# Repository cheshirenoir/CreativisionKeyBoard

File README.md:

# CreativisionKeyBoard
Replacement Moving Key Keyboard for the VTech Creativision, AKA the Dick Smith Wizzard

An attempt to map the Moving Key Keyboard then convert it into a functional PCB 

This design is released under a CC-BY-SA license. Remix, but always share!

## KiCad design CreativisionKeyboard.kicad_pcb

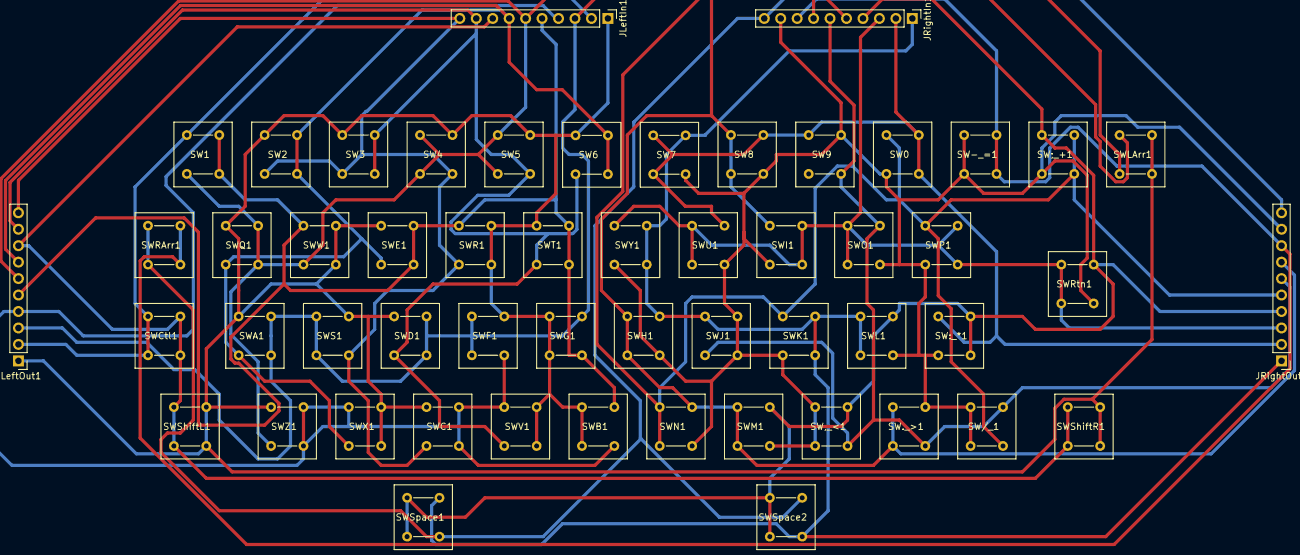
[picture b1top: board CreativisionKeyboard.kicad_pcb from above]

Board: 2 copper layers, 54 parts (0 on the bottom side), 20 nets.

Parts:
JLeftIn1: Conn_01x10_Female; PinHeader_1x10_P2.54mm_Vertical
JLeftOut1: Conn_01x10_Female; PinHeader_1x10_P2.54mm_Vertical
JRightIn1: Conn_01x10_Female; PinHeader_1x10_P2.54mm_Vertical
JRightOut1: Conn_01x10_Female; PinHeader_1x10_P2.54mm_Vertical
SW0: 0; pva1oah31.2nv2
SW1: 1; pva1oah31.2nv2
SW2: 2; pva1oah31.2nv2
SW3: 3; pva1oah31.2nv2
SW4: 4; pva1oah31.2nv2
SW5: 5; pva1oah31.2nv2
SW6: 6; pva1oah31.2nv2
SW7: 7; pva1oah31.2nv2
SW8: 8; pva1oah31.2nv2
SW9: 9; pva1oah31.2nv2
SW,_<1: Comma LT; pva1oah31.2nv2
SW-_=1: Minus Equals; pva1oah31.2nv2
SW._>1: Period GT; pva1oah31.2nv2
SW/_1: Slash QMark; pva1oah31.2nv2
SW:_*1: Colon Star; pva1oah31.2nv2
SW;_+1: SemiColon Plus; pva1oah31.2nv2
SWA1: A; pva1oah31.2nv2
SWB1: B; pva1oah31.2nv2
SWC1: C; pva1oah31.2nv2
SWCtl1: Ctrl; pva1oah31.2nv2
SWD1: D; pva1oah31.2nv2
SWE1: E; pva1oah31.2nv2
SWF1: F; pva1oah31.2nv2
SWG1: G; pva1oah31.2nv2
SWH1: H; pva1oah31.2nv2
SWI1: I; pva1oah31.2nv2
SWJ1: J; pva1oah31.2nv2
SWK1: K; pva1oah31.2nv2
SWL1: L; pva1oah31.2nv2
SWLArr1: <-; pva1oah31.2nv2
SWM1: M; pva1oah31.2nv2
SWN1: N; pva1oah31.2nv2
SWO1: O; pva1oah31.2nv2
SWP1: P; pva1oah31.2nv2
SWQ1: Q; pva1oah31.2nv2
SWR1: R; pva1oah31.2nv2
SWRArr1: ->; pva1oah31.2nv2
SWRtn1: Return; pva1oah31.2nv2
SWS1: S; pva1oah31.2nv2
SWShiftL1: Shift Left; pva1oah31.2nv2
SWShiftR1: Shift Righ; pva1oah31.2nv2
SWSpace1, SWSpace2: Space; pva1oah31.2nv2
SWT1: T; pva1oah31.2nv2
SWU1: U; pva1oah31.2nv2
SWV1: V; pva1oah31.2nv2
SWW1: W; pva1oah31.2nv2
SWX1: X; pva1oah31.2nv2
SWY1: Y; pva1oah31.2nv2
SWZ1: Z; pva1oah31.2nv2

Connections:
unnamed: JLeftIn1.1, JLeftOut1.1, SW2.1, SW3.1, SW4.2, SW5.2, SW6.1, SWA1.1, SWB1.1, SWB1.3, SWC1.1, SWD1.1, SWE1.1, SWF1.2, SWG1.1, SWG1.3, SWLArr1.2, SWLArr1.4, SWQ1.1, SWR1.2, SWR1.4, SWS1.2, SWShiftL1.2, SWShiftL1.4, SWShiftR1.2, SWShiftR1.4, SWT1.1, SWV1.2, SWV1.4, SWW1.2, SWW1.4, SWX1.2, SWX1.4, SWZ1.1
unnamed: JLeftIn1.2, JLeftOut1.2, SW1.1, SWCtl1.1, SWCtl1.3
unnamed: JLeftIn1.3, JLeftOut1.3, SWA1.2, SWA1.4, SWD1.2, SWD1.4, SWF1.1, SWF1.3, SWG1.2, SWLArr1.1, SWS1.1, SWS1.3
unnamed: JLeftIn1.4, JLeftOut1.4, SWB1.4, SWC1.2, SWC1.4, SWF1.4, SWV1.1, SWX1.1, SWZ1.2, SWZ1.4
unnamed: JLeftIn1.5, JLeftOut1.5, SW1.2, SW1.4, SWB1.2, SWE1.2, SWE1.4, SWG1.4, SWR1.1, SWT1.2, SWT1.4, SWW1.1
unnamed: JLeftIn1.6, JLeftOut1.6, SW1.3, SW4.1, SW4.3, SW5.1, SW5.3, SWLArr1.3, SWQ1.2, SWQ1.4, SWW1.3, SWZ1.3
unnamed: JLeftIn1.7, JLeftOut1.7, SW2.2, SW2.4, SW6.2, SW6.4, SWA1.3, SWE1.3, SWQ1.3, SWX1.3
unnamed: JLeftIn1.8, JLeftOut1.8, SWCtl1.2, SWCtl1.4, SWShiftL1.1, SWShiftL1.3, SWShiftR1.1, SWShiftR1.3
unnamed: JLeftIn1.9, JLeftOut1.9, SW3.2, SW3.4, SW5.4, SW6.3, SWD1.3, SWT1.3, SWV1.3
unnamed: JLeftIn1.10, JLeftOut1.10, SW2.3, SW3.3, SW4.4, SWC1.3, SWR1.3, SWS1.4
unnamed: JRightIn1.1, JRightOut1.1, SW7.2, SWH1.2, SWJ1.1, SWK1.2, SWK1.4, SWL1.1, SWL1.3, SWSpace1.2, SWSpace2.4, SWY1.2, SWY1.4
unnamed: JRightIn1.2, JRightOut1.2, SW0.2, SW0.4, SW7.1, SW7.3, SW8.2, SW9.1, SW:_*1.1, SWU1.2
unnamed: JRightIn1.3, JRightOut1.3, SWI1.2, SWI1.4, SWO1.1, SWO1.3, SWP1.2, SWP1.4, SWRtn1.1, SWRtn1.3, SWU1.1, SWU1.3, SWY1.1
unnamed: JRightIn1.4, JRightOut1.4, SW,_<1.2, SW:_*1.2, SW:_*1.4, SW;_+1.1, SWL1.2, SWM1.2, SWRtn1.2, SWSpace1.1, SWSpace1.3, SWSpace2.1, SWSpace2.3
unnamed: JRightIn1.5, JRightOut1.5, SW0.1, SW/_1.4, SW;_+1.2, SW;_+1.4, SWK1.1, SWN1.1, SWN1.3, SWP1.1
unnamed: JRightIn1.6, JRightOut1.6, SW9.4, SW,_<1.4, SW._>1.4, SW/_1.2, SWJ1.3, SWO1.2
unnamed: JRightIn1.7, JRightOut1.7, SW8.1, SW8.3, SW._>1.1, SW._>1.3, SWH1.1, SWH1.3, SWI1.1, SWM1.1, SWM1.3, SWN1.2
unnamed: JRightIn1.8, JRightOut1.8, SW-_=1.2, SW-_=1.4, SWRArr1.2, SWRArr1.4
unnamed: JRightIn1.9, JRightOut1.9, SW0.3, SW7.4, SW8.4, SW9.2, SW,_<1.1, SW,_<1.3, SW-_=1.1, SW-_=1.3, SW._>1.2, SW/_1.1, SW/_1.3, SW:_*1.3, SW;_+1.3, SWH1.4, SWI1.3, SWJ1.2, SWJ1.4, SWK1.3, SWL1.4, SWM1.4, SWN1.4, SWO1.4, SWP1.3, SWRtn1.4, SWU1.4, SWY1.3
unnamed: JRightIn1.10, JRightOut1.10, SWRArr1.1, SWRArr1.3, SWSpace1.4, SWSpace2.2

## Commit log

2021-01-11 Add files via upload
    Partially mapped keyboard Schematic. There WILL be bugs here and there WILL be incomplete sections. More versions will follow.
2021-02-10 Add files via upload
    This is the fully mapped out version. It appears to be impossible to build...
2021-03-14 Add files via upload
    First complete PCB. This has been tested as individual keys, but not as a final schematic.
    Built around this key: https://au.mouser.com/Electronic-Components/
2021-03-14 Add files via upload
    The PCB in PDF format.
